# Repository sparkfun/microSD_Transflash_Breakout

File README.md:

SparkFun microSD Transflash Breakout
===================================
![SparkFun microSD Transflash Breakout
](https://cdn.sparkfun.com//assets/parts/3/0/6/00544-01.jpg)

[*SparkFun microSD Transflash Breakout
 (BOB-00544)*](https://www.sparkfun.com/products/544)

 Breakout board for the microSD socket that is not much bigger than your fingernail. Compatible with the SPI interface found on any SD card, this tiny form factor was created for cell phone storage and is perfect for your next MP3 project! 

Repository Contents
-------------------

* **/Hardware** - All Eagle design files (.brd, .sch)

License Information
-------------------
The hardware is released under [Creative Commons ShareAlike 4.0 International](https://creativecommons.org/licenses/by-sa/4.0/).

Distributed as-is; no warranty is given.

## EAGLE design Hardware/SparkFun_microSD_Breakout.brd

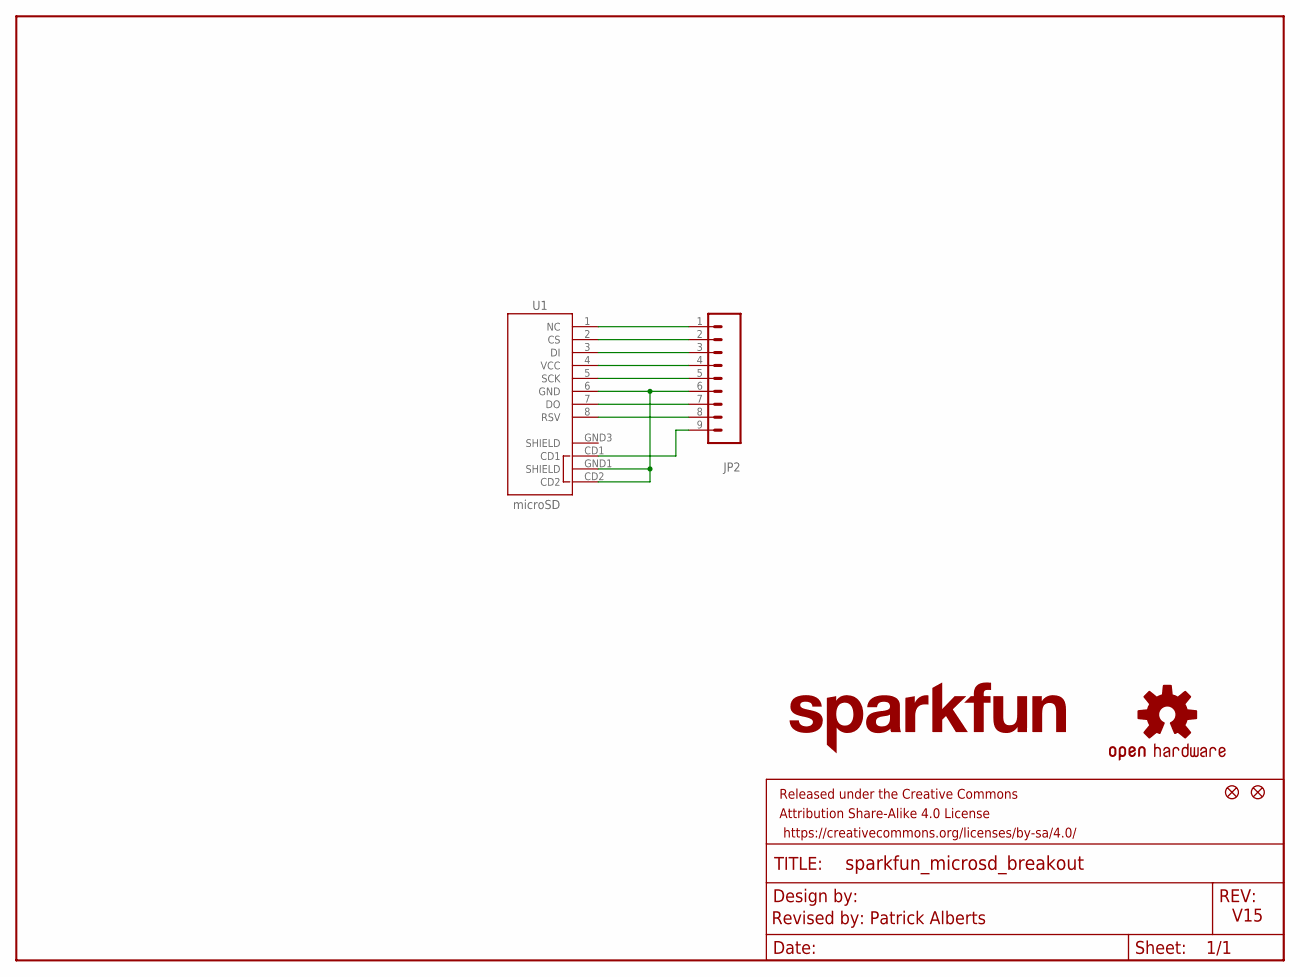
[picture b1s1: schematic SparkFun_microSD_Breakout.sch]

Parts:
FID1, FID2: FIDUCIALUFIDUCIAL; MICRO-FIDUCIAL
FRAME1: FRAME-LETTER; CREATIVE_COMMONS
JP2: M09; 1X09
LOGO1: OSHW-LOGOL; OSHW-LOGO-L
LOGO2: SFE_LOGO_NAME.1_INCH; SFE_LOGO_NAME_.1
U1: microSD; MICROSD_1:1

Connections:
CD1: JP2.9, U1.CD1
CS: JP2.2, U1.2 (CS)
DI: JP2.3, U1.3 (DI)
DO: JP2.7, U1.7 (DO)
GND: JP2.6, U1.6 (GND), U1.CD2, U1.GND1 (SHIELD)
NC: JP2.1, U1.1 (NC)
RSV: JP2.8, U1.8 (RSV)
SCK: JP2.5, U1.5 (SCK)
VCC: JP2.4, U1.4 (VCC)

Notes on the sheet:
V15
Revised by: Patrick Alberts

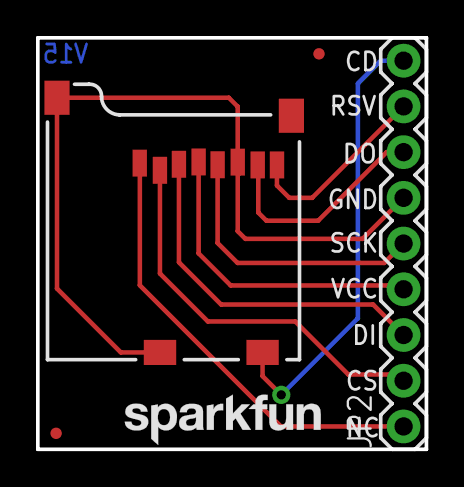
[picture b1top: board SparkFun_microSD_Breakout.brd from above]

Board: 2 copper layers, 21.6 x 22.9 mm, 7 parts (1 on the bottom side), 9 nets.

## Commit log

2015-03-03 Adding hardware files, updating README
2015-05-07 Changed to 9 pin header, BO leftover pins.
2015-05-13 Fixed pin out.
2015-05-14 Correct SCH and Version #
2024-10-11 Convert files to eagle 7 format

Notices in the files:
parts and their libraries:
SparkFun-Connectors: Licensing: Creative Commons ShareAlike 4.0 International - https://creativecommons.org/licenses/by-sa/4.0
SparkFun-Aesthetics: Released under the Creative Commons Attribution Share-Alike 4.0 License
SparkFun-Aesthetics: Released under the Creative Commons
